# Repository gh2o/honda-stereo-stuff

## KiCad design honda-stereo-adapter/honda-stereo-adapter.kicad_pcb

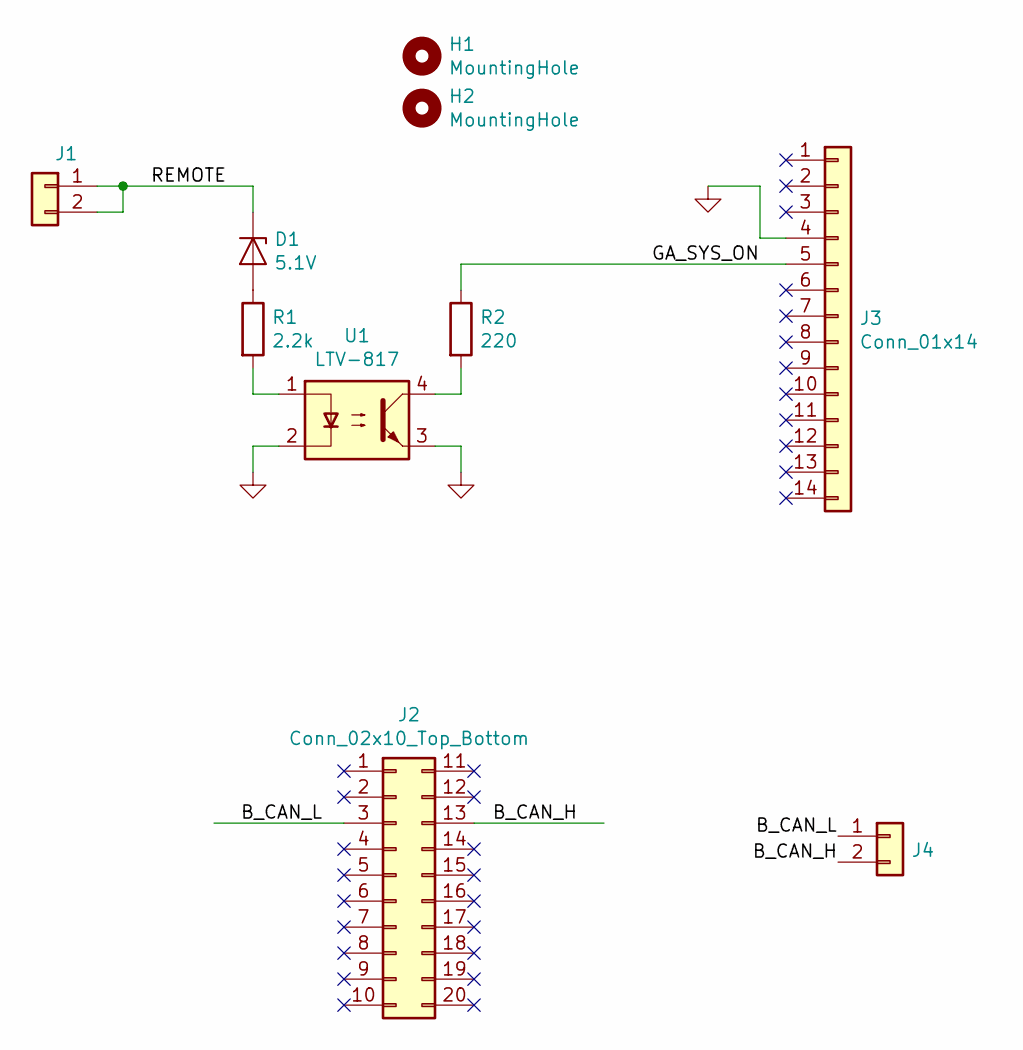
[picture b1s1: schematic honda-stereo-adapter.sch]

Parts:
D1: 5.1V; D_DO-35_SOD27_P7.62mm_Horizontal
H1, H2: MountingHole; MountingHole_3.2mm_M3
J1, J4: Conn_01x02; Keystone_7822_Blade_W6.35mm
J2: Conn_02x10_Top_Bottom; JAE_MF34020NF1_Honda
J3: Conn_01x14; TE_917534_Honda
R1: 2.2k; R_Axial_DIN0207_L6.3mm_D2.5mm_P7.62mm_Horizontal
R2: 220; R_Axial_DIN0207_L6.3mm_D2.5mm_P7.62mm_Horizontal
U1: LTV-817; DIP-4_W7.62mm

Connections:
/B_CAN_H: J2.13, J4.2
/B_CAN_L: J2.3, J4.1
/GA_SYS_ON: J3.5, R2.1
/REMOTE: D1.1 (K), J1.1, J1.2
GND: J3.4, U1.2, U1.3
unnamed: D1.2 (A), R1.1
unnamed: R1.2, U1.1
unnamed: R2.2, U1.4

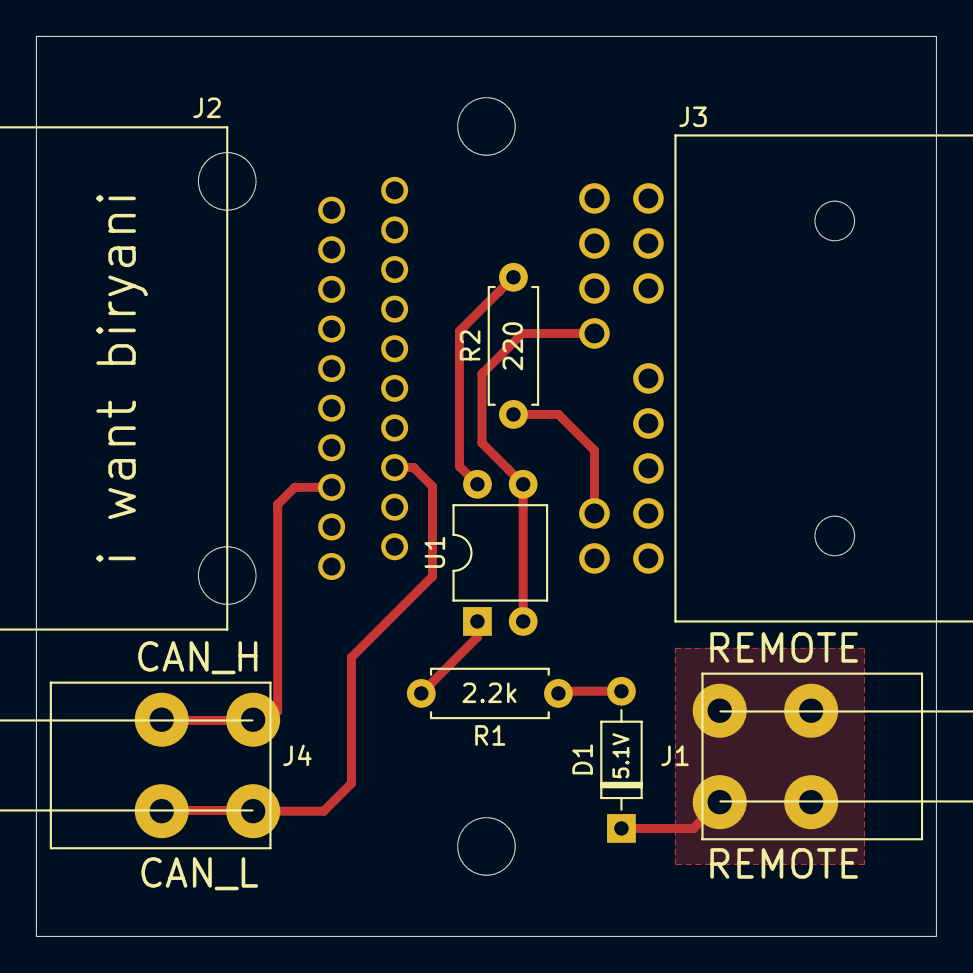
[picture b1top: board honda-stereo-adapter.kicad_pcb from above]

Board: 2 copper layers, 50.0 x 50.0 mm, 10 parts (0 on the bottom side), 8 nets.

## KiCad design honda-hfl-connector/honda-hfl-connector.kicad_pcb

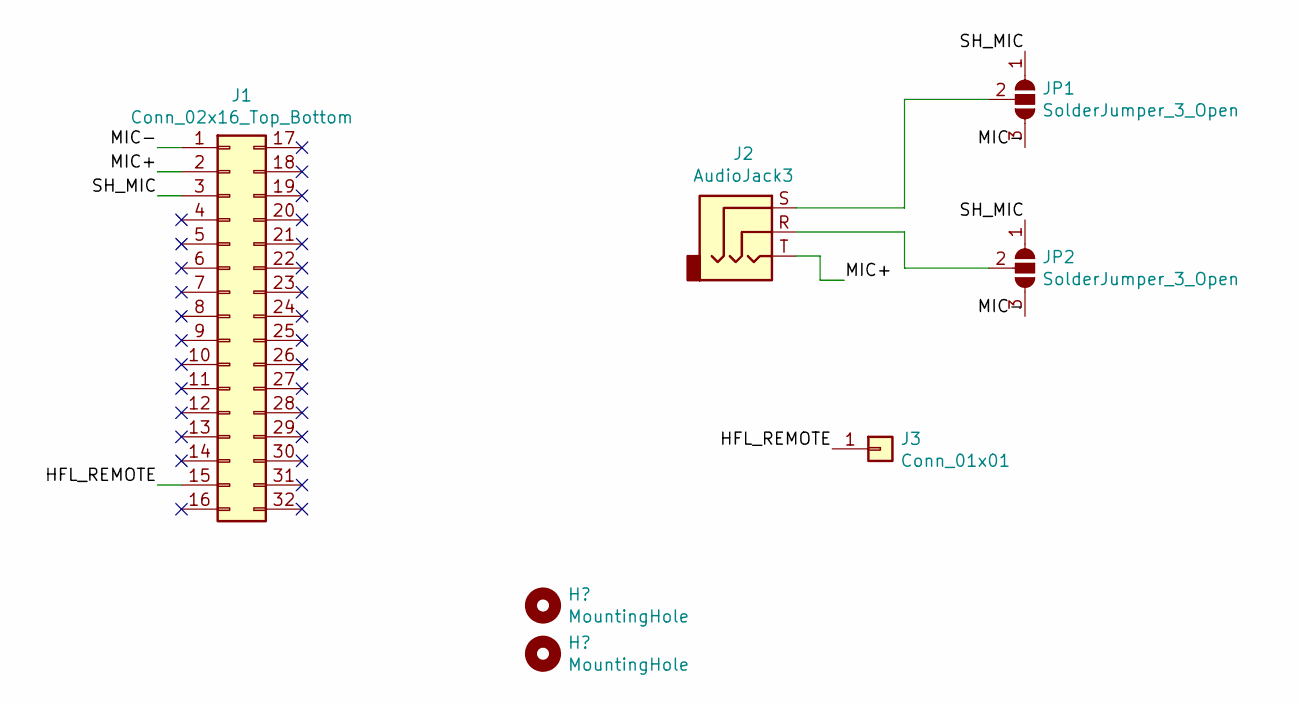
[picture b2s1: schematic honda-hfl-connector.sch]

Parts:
J1: Conn_02x16_Top_Bottom; JAE_MF34032NF2_Honda
J2: AudioJack3; Jack_3.5mm_CUI_SJ1-3533NG_Horizontal
J3: Conn_01x01; Keystone_4966
JP1, JP2: SolderJumper_3_Open; SolderJumper-3_P1.3mm_Open_Pad1.0x1.5mm

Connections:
/HFL_REMOTE: J1.15, J3.1
/MIC+: J1.2, J2.T
/MIC-: J1.1, JP1.3 (B), JP2.3 (B)
/SH_MIC: J1.3, JP1.1 (A), JP2.1 (A)
unnamed: J2.R, JP2.2 (C)
unnamed: J2.S, JP1.2 (C)

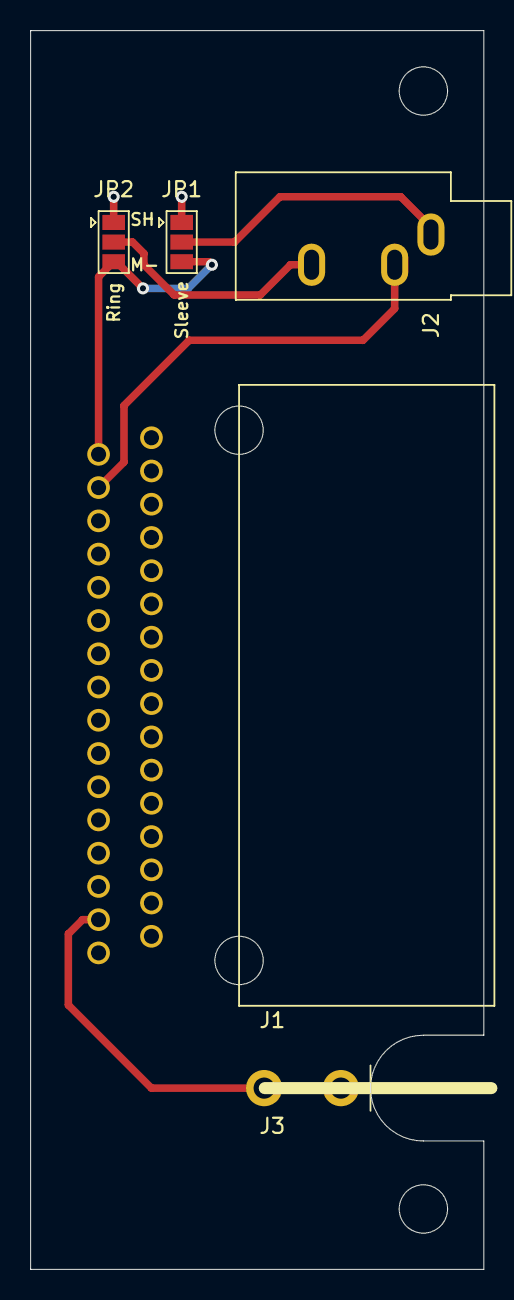
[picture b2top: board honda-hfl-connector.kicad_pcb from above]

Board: 2 copper layers, 30.0 x 82.0 mm, 7 parts (0 on the bottom side), 6 nets.

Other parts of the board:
H1, H2: MountingHole; MountingHole_3.2mm_M3
